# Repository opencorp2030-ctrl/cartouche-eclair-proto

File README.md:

# CARTOUCHE Drive

A small USB-C drive for an M.2 2230 NVMe SSD, built around the JMicron JMS583
bridge (USB 3.2 Gen 2, 10 Gb/s → PCIe Gen 3 ×2). It is the prototype drive for
[CARTOUCHE](https://cartouche.candygate.eu), a local AI that runs from a USB drive.

**Status:** schematic v0.1 (ERC 0). PCB v0.4 — 36 × 46 mm, 4 layers (In1 GND, In2 GND + 1.0 V island), 9 high-speed pairs as straight coupled pairs. Impedance from a 2D field solver (`tools/impedance.py`, JLC04161H-7628, with solder mask): USB 3.2 pairs 0.20/0.10 mm ≈ 86 Ω (target 90 Ω ±10 %), PCIe and REFCLK pairs 0.30/0.20 mm ≈ 89 Ω (target 85 Ω ±15 %), GND stitching. DRC: 0 unconnected, 0 schematic mismatch, 2 silkscreen warnings. Fabrication files in `hardware/fab/` (Gerbers zip, JLCPCB BOM and CPL). **Prototype, not verified:** JMS583 must be consigned (0 stock at JLCPCB), CPL rotations to check in the JLCPCB viewer, LED polarity assumed active-low.

## Blocks

| Block | Parts |
|---|---|
| USB-C (sink, 5 V) | Molex 105450-0101, CC pull-downs 5.1 kΩ, 100 nF on each SuperSpeed TX line |
| Bridge | JMS583 (QFN-64 8×8, 0.4 mm), 25 MHz crystal, REXT 12 kΩ 1 %, reset RC, SPI flash |
| Chip power | JMS583 internal regulators: 5 V → 1.0 V (buck, 4.7 µH) and 5 V → 3.3 V (LDO, chip only) |
| SSD power | TPS82130 3 A buck, 5 V → 3.3 V, 330 µF bulk |
| SSD | LOTES APCI0113 M.2 key M socket, 2 PCIe lanes, 220 nF on each PCIe TX line |

## Files

- `hardware/` — KiCad 9 project (`cartouche-drive.kicad_sch`), local libraries in `hardware/lib/`
- `hardware/cartouche-drive-schematic.pdf` — schematic export
- `tools/gen_schematic.py` — the connection list that generates the schematic
- `tools/build_pcb.py` — board, placement, planes and fan-out vias (KiCad Python)
- `tools/route_pcb.py` — net classes and Freerouting run

## References

- JMS583 datasheet PDS-17001 rev 1.0 (JMicron) — pin-out and required parts
- Part footprints: LCSC / EasyEDA libraries (LOTES C841669, Molex C134092, TPS82130 C473914)

## Sponsors

Thank you to the companies that support this open-source board:

- **[AISLER](https://aisler.net) is the PCB sponsor of this project** (boards, stencils and shipping, made in Europe). The AISLER logo is printed on the back of the board (placeholder on `B.Silkscreen`, `tools/aisler_logo.py`). Order your own with the button above.
- **[JMicron](https://www.jmicron.com)**, through its distributor **[BONMECK](https://www.bonmeck.com)**, provides free JMS583 bridge chip samples for the first prototypes.

Results of the prototypes, good or bad, will be published here.

## License

Open source. Hardware (`hardware/`, `docs/`): [CERN-OHL-S-2.0](LICENSE-HARDWARE). Tools (`tools/`): MIT.
See [LICENSE](LICENSE). Third-party libraries used in the KiCad project (KiCad standard libraries, LCSC/EasyEDA
footprints and 3D models) stay under their own licenses.

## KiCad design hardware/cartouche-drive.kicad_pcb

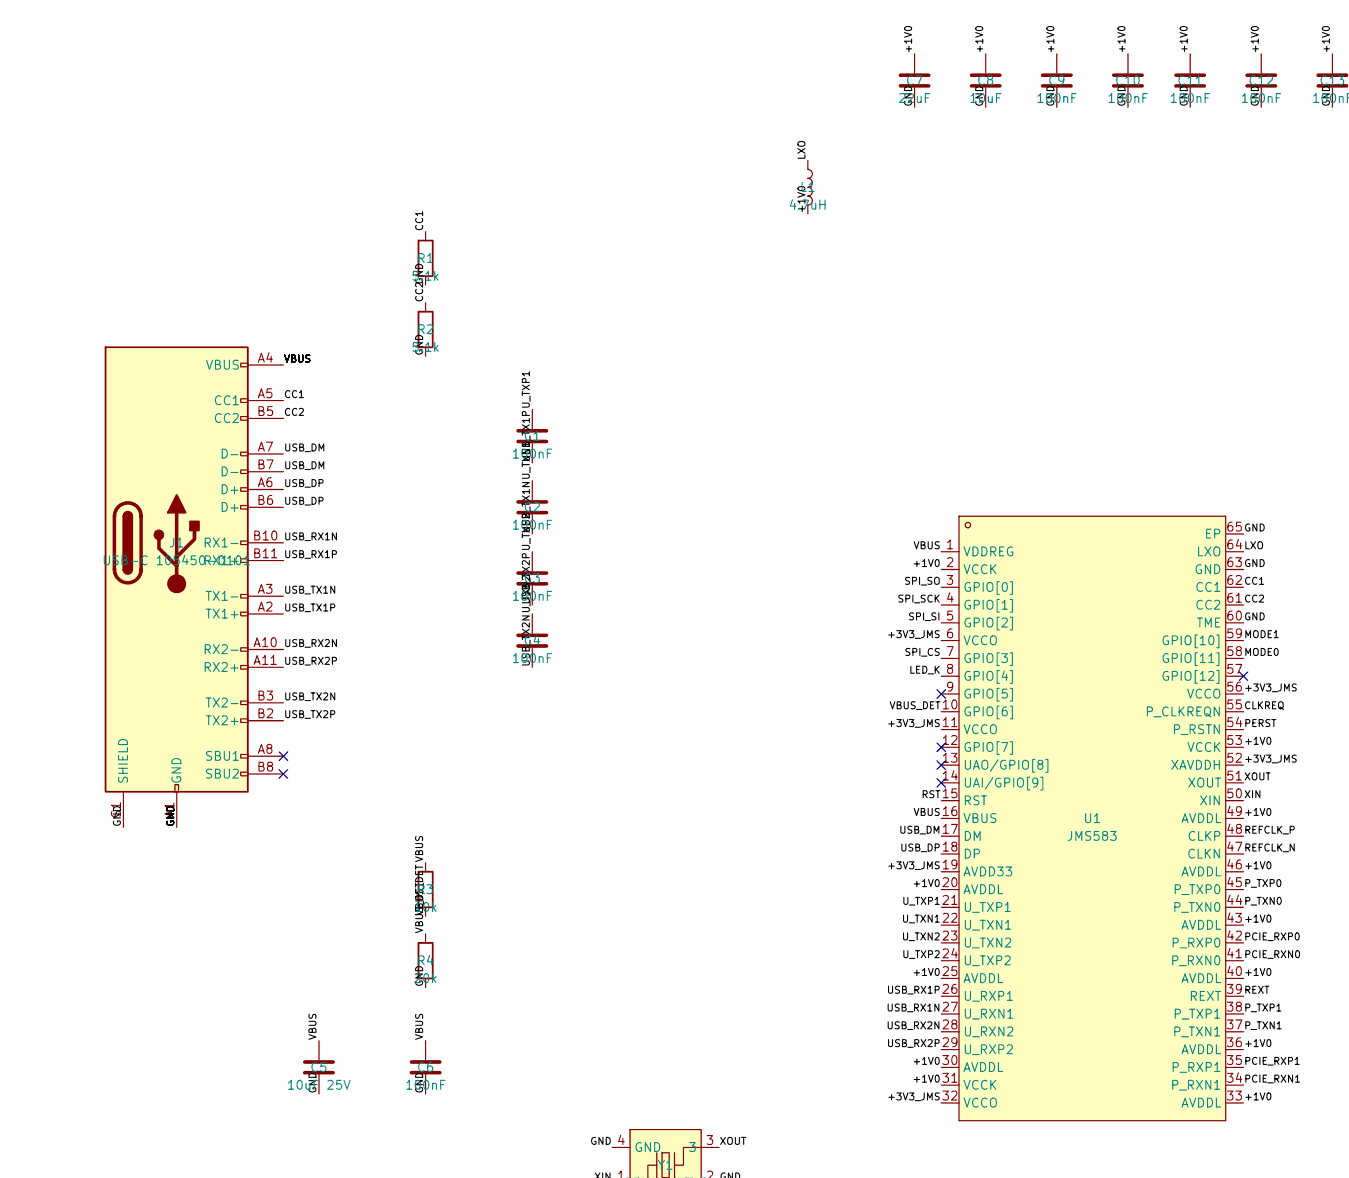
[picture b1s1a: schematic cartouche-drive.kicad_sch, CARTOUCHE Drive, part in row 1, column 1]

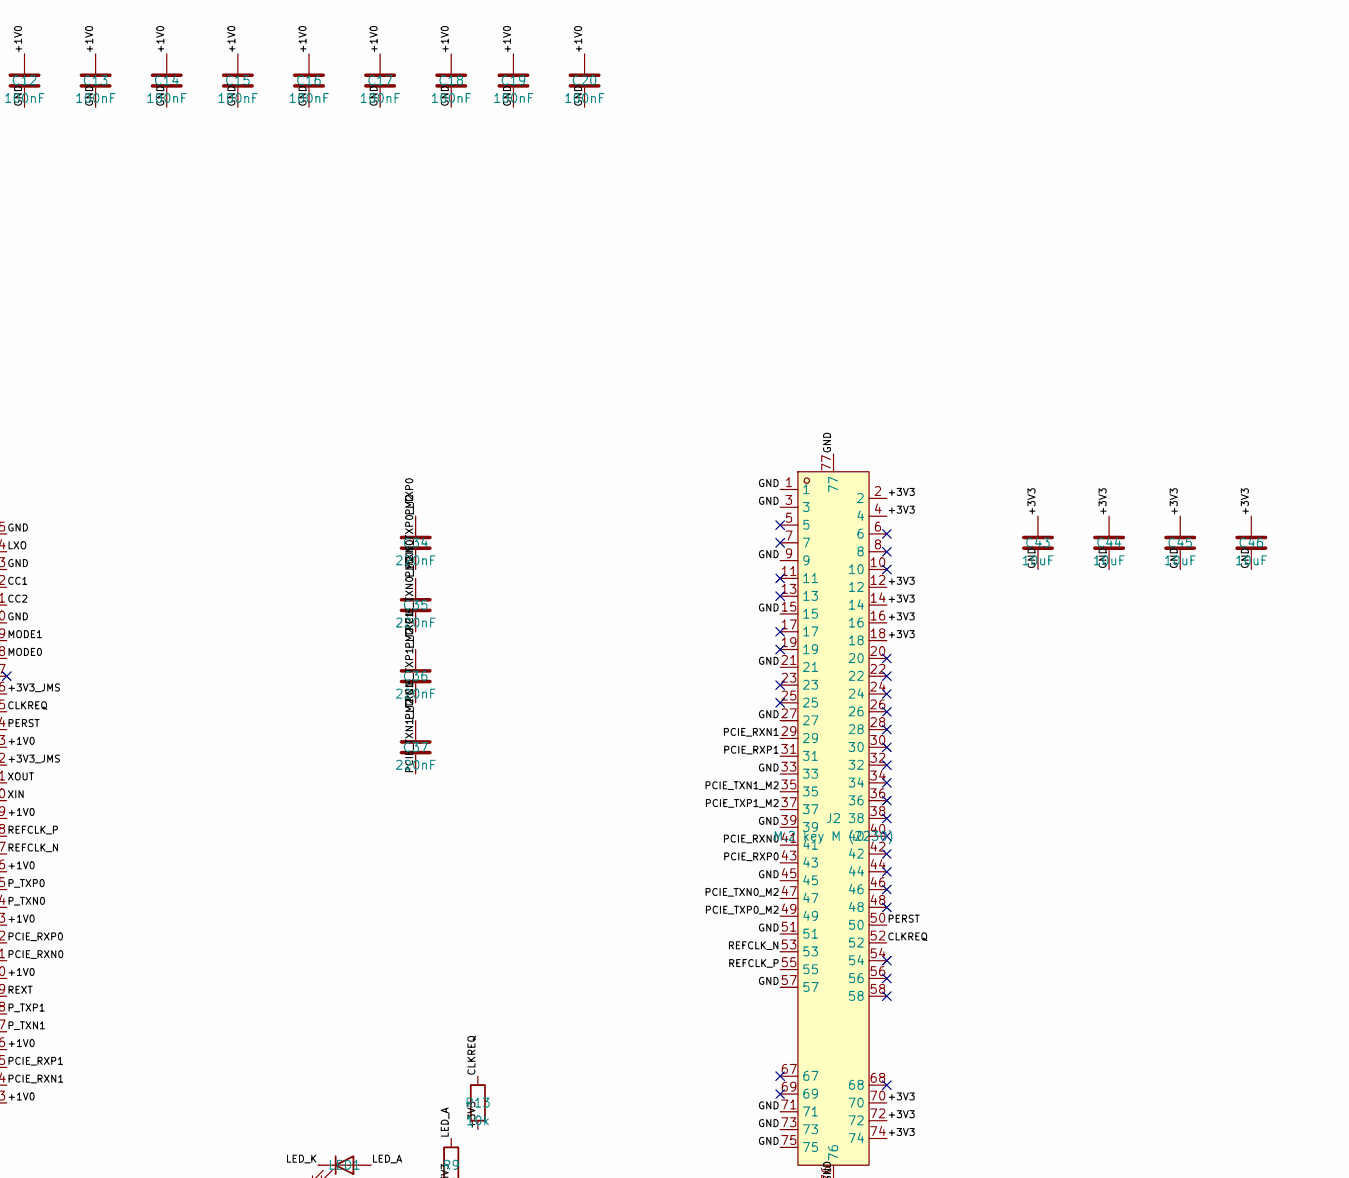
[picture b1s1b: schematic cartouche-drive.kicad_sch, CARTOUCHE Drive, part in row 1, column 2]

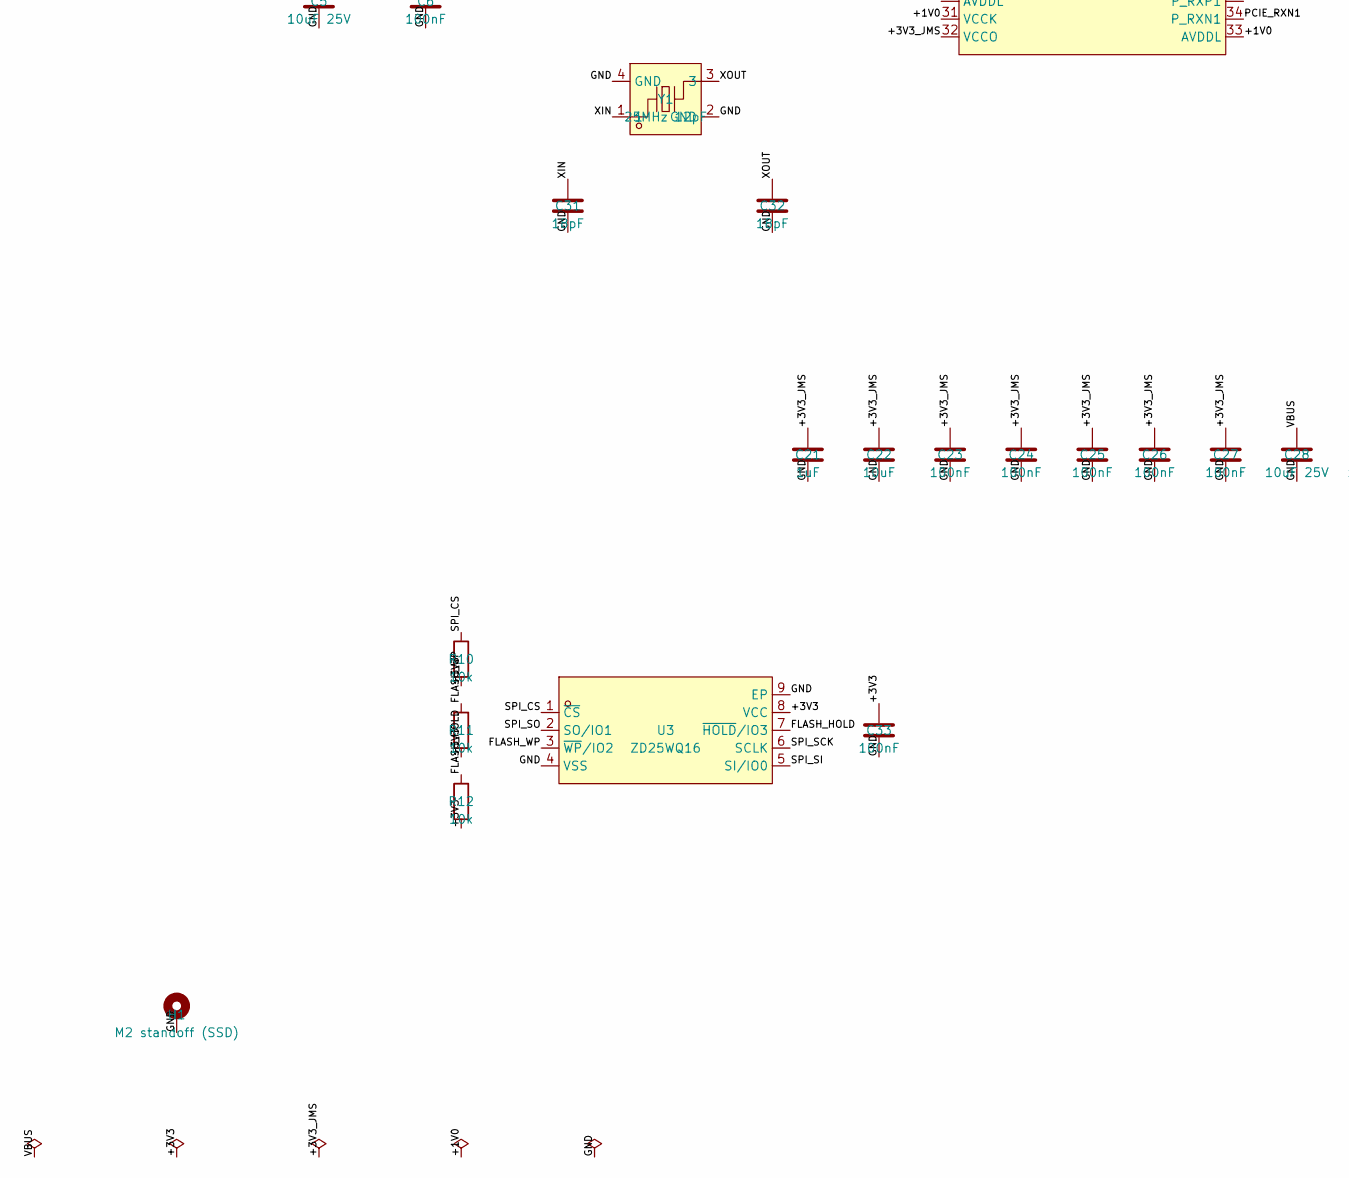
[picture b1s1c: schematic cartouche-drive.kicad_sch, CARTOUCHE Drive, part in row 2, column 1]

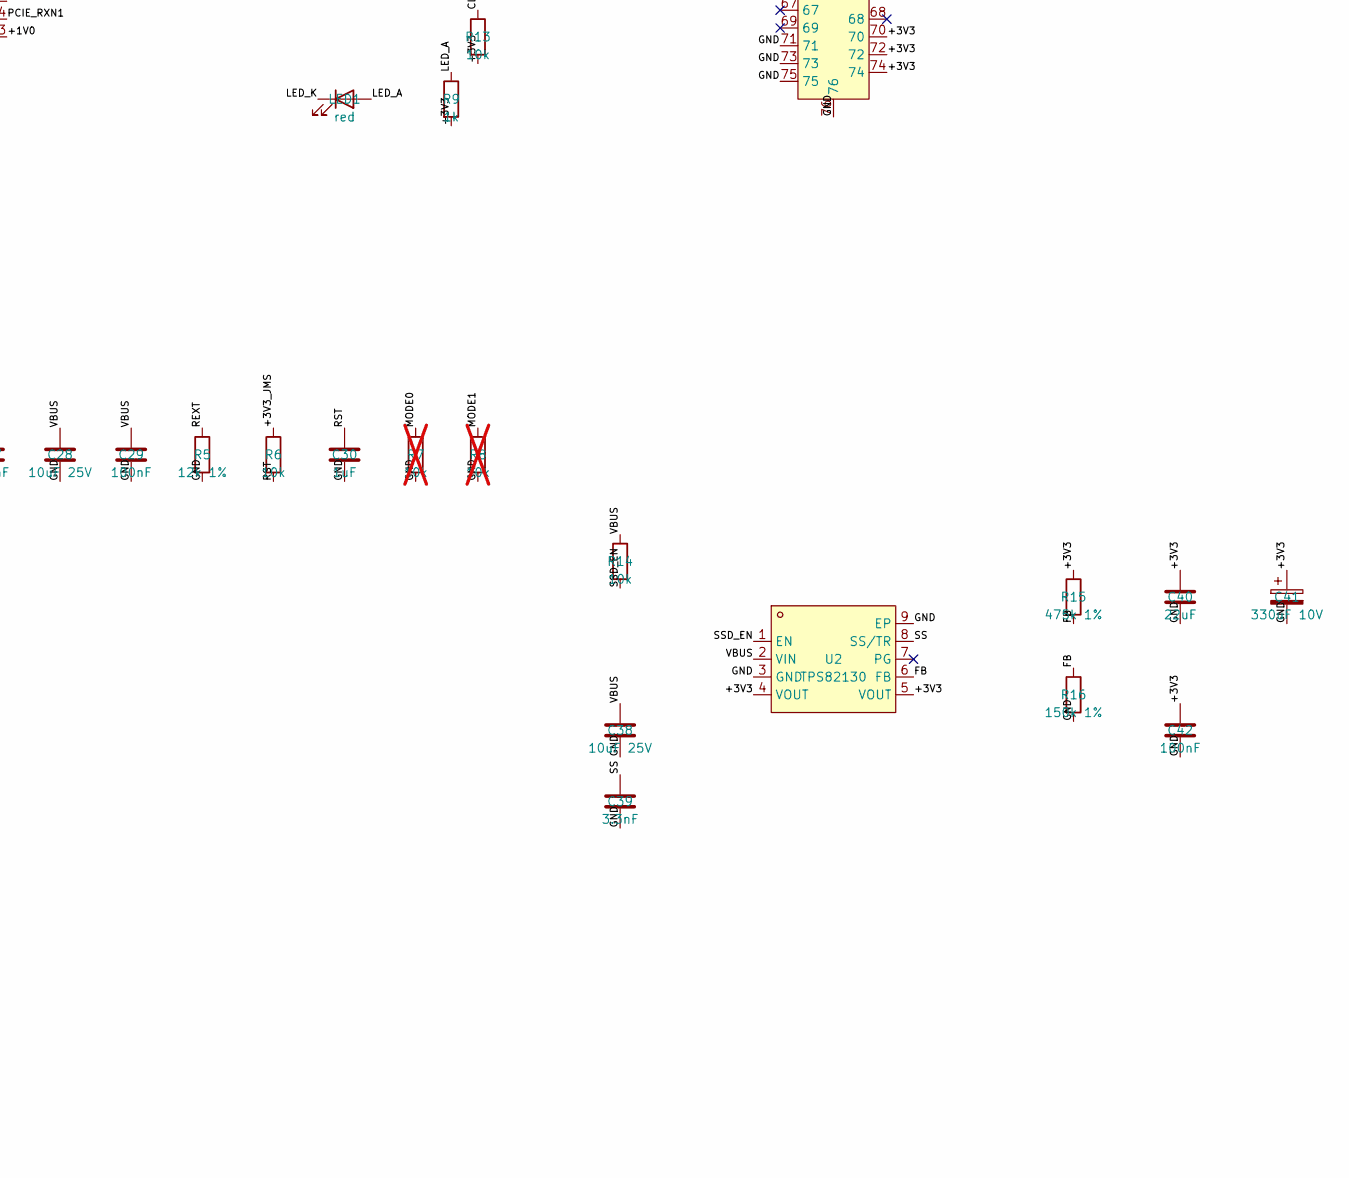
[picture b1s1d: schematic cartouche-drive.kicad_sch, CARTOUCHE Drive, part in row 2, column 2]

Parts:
C1, C2, C3, C4: 100nF; C_0201_0603Metric; LCSC C76934
C5, C28, C38: 10uF 25V; C_0805_2012Metric; LCSC C15850
C6, C9, C10, C11, C12, C13, C14, C15, C16, C17, C18, C19, C20, C23, C24, C25, C26, C27, C29, C33, C42: 100nF; C_0402_1005Metric; LCSC C1525
C7, C40: 22uF; C_0805_2012Metric; LCSC C45783
C8, C22, C43, C44, C45, C46: 10uF; C_0402_1005Metric; LCSC C15525
C21, C30: 1uF; C_0402_1005Metric; LCSC C52923
C31, C32: 18pF; C_0402_1005Metric; LCSC C1549
C34, C35, C36, C37: 220nF; C_0201_0603Metric; LCSC C76932
C39: 3.3nF; C_0402_1005Metric; LCSC C1536
C41: 330uF 10V; CP_EIA-7343-31_Kemet-D; LCSC C105408
H1: M2 standoff (SSD); MountingHole_2.2mm_M2_Pad_Via
J1: USB-C 105450-0101; USB_C_Receptacle_Molex_105450-0101; LCSC C134092
J2: M.2 key M (2230); CONN-SMD_APCI0113-P001A; LCSC C841669
L1: 4.7uH; L_1008_2520Metric; LCSC C383386
LED1: red; LED_0603_1608Metric; LCSC C2286
R1, R2: 5.1k; R_0402_1005Metric; LCSC C25905
R3, R6, R10, R11, R12, R13, R14: 10k; R_0402_1005Metric; LCSC C25744
R4: 20k; R_0402_1005Metric; LCSC C25765
R5: 12k 1%; R_0402_1005Metric; LCSC C25752
R7, R8: 10k; R_0402_1005Metric; LCSC C25744; not fitted
R9: 1k; R_0402_1005Metric; LCSC C11702
R15: 475k 1%; R_0402_1005Metric; LCSC C5713272
R16: 150k 1%; R_0402_1005Metric; LCSC C2909320
U1: JMS583; QFN-64_L8.0-W8.0-P0.40-TL-EP4.5; LCSC C9900110183
U2: TPS82130; USIP-8_L3.0-W2.8-P0.65-TL-EP; LCSC C473914
U3: ZD25WQ16; USON-8_L3.0-W2.0-P0.50-BL-EP; LCSC C7304007
Y1: 25MHz 12pF; CRYSTAL-SMD_4P-L1.6-W1.2-BL; LCSC C7301914

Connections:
/+1V0: C7.1, C8.1, C9.1, C10.1, C11.1, C12.1, C13.1, C14.1, C15.1, C16.1, C17.1, C18.1, C19.1, C20.1, L1.2, U1.2 (VCCK), U1.20 (AVDDL), U1.25 (AVDDL), U1.30 (AVDDL), U1.31 (VCCK), U1.33 (AVDDL), U1.36 (AVDDL), U1.40 (AVDDL), U1.43 (AVDDL), U1.46 (AVDDL), U1.49 (AVDDL), U1.53 (VCCK)
/+3V3: C33.1, C40.1, C41.1, C42.1, C43.1, C44.1, C45.1, C46.1, J2.2, J2.4, J2.12, J2.14, J2.16, J2.18, J2.70, J2.72, J2.74, R9.2, R10.2, R11.2, R12.2, R13.2, R15.1, U2.4 (VOUT), U2.5 (VOUT), U3.8 (VCC)
/+3V3_JMS: C21.1, C22.1, C23.1, C24.1, C25.1, C26.1, C27.1, R6.1, U1.6 (VCCO), U1.11 (VCCO), U1.19 (AVDD33), U1.32 (VCCO), U1.52 (XAVDDH), U1.56 (VCCO)
/CC1: J1.A5 (CC1), R1.1, U1.62 (CC1)
/CC2: J1.B5 (CC2), R2.1, U1.61 (CC2)
/CLKREQ: J2.52, R13.1, U1.55 (P_CLKREQN)
/FB: R15.2, R16.1, U2.6 (FB)
/FLASH_HOLD: R12.1, U3.7 (~HOLD/IO3)
/FLASH_WP: R11.1, U3.3 (~WP/IO2)
/GND: C5.2, C6.2, C7.2, C8.2, C9.2, C10.2, C11.2, C12.2, C13.2, C14.2, C15.2, C16.2, C17.2, C18.2, C19.2, C20.2, C21.2, C22.2, C23.2, C24.2, C25.2, C26.2, C27.2, C28.2, C29.2, C30.2, C31.2, C32.2, C33.2, C38.2, C39.2, C40.2, C41.2, C42.2, C43.2, C44.2, C45.2, C46.2, H1.1, J1.A1 (GND), J1.A12 (GND), J1.B1 (GND), J1.B12 (GND), J1.S1 (SHIELD), J2.1, J2.3, J2.9, J2.15, J2.21, J2.27, J2.33, J2.39, J2.45, J2.51, J2.57, J2.71, J2.73, J2.75, J2.76, J2.77, R1.2, R2.2, R4.2, R5.2, R7.2, R8.2, R16.2, U1.60 (TME), U1.63 (GND), U1.65 (EP), U2.3 (GND), U2.9 (EP), U3.4 (VSS), U3.9 (EP), Y1.2 (GND), Y1.4 (GND)
/LED_A: LED1.2 (A), R9.1
/LED_K: LED1.1 (K), U1.8 (GPIO[4])
/LXO: L1.1, U1.64 (LXO)
/MODE0: R7.1, U1.58 (GPIO[11])
/MODE1: R8.1, U1.59 (GPIO[10])
/PCIE_RXN0: J2.41, U1.41 (P_RXN0)
/PCIE_RXN1: J2.29, U1.34 (P_RXN1)
/PCIE_RXP0: J2.43, U1.42 (P_RXP0)
/PCIE_RXP1: J2.31, U1.35 (P_RXP1)
/PCIE_TXN0_M2: C35.2, J2.47
/PCIE_TXN1_M2: C37.2, J2.35
/PCIE_TXP0_M2: C34.2, J2.49
/PCIE_TXP1_M2: C36.2, J2.37
/PERST: J2.50, U1.54 (P_RSTN)
/P_TXN0: C35.1, U1.44 (P_TXN0)
/P_TXN1: C37.1, U1.37 (P_TXN1)
/P_TXP0: C34.1, U1.45 (P_TXP0)
/P_TXP1: C36.1, U1.38 (P_TXP1)
/REFCLK_N: J2.53, U1.47 (CLKN)
/REFCLK_P: J2.55, U1.48 (CLKP)
/REXT: R5.1, U1.39 (REXT)
/RST: C30.1, R6.2, U1.15 (RST)
/SPI_CS: R10.1, U1.7 (GPIO[3]), U3.1 (~CS)
/SPI_SCK: U1.4 (GPIO[1]), U3.6 (SCLK)
/SPI_SI: U1.5 (GPIO[2]), U3.5 (SI/IO0)
/SPI_SO: U1.3 (GPIO[0]), U3.2 (SO/IO1)
/SS: C39.1, U2.8 (SS/TR)
/SSD_EN: R14.2, U2.1 (EN)
/USB_DM: J1.A7 (D-), J1.B7 (D-), U1.17 (DM)
/USB_DP: J1.A6 (D+), J1.B6 (D+), U1.18 (DP)
/USB_RX1N: J1.B10 (RX1-), U1.27 (U_RXN1)
/USB_RX1P: J1.B11 (RX1+), U1.26 (U_RXP1)
/USB_RX2N: J1.A10 (RX2-), U1.28 (U_RXN2)
/USB_RX2P: J1.A11 (RX2+), U1.29 (U_RXP2)
/USB_TX1N: C2.2, J1.A3 (TX1-)
/USB_TX1P: C1.2, J1.A2 (TX1+)
/USB_TX2N: C4.2, J1.B3 (TX2-)
/USB_TX2P: C3.2, J1.B2 (TX2+)
/U_TXN1: C2.1, U1.22 (U_TXN1)
/U_TXN2: C4.1, U1.23 (U_TXN2)
/U_TXP1: C1.1, U1.21 (U_TXP1)
/U_TXP2: C3.1, U1.24 (U_TXP2)
/VBUS: C5.1, C6.1, C28.1, C29.1, C38.1, J1.A4 (VBUS), J1.A9 (VBUS), J1.B4 (VBUS), J1.B9 (VBUS), R3.1, R14.1, U1.1 (VDDREG), U1.16 (VBUS), U2.2 (VIN)
/VBUS_DET: R3.2, R4.1, U1.10 (GPIO[6])
/XIN: C31.1, U1.50 (XIN), Y1.1
/XOUT: C32.1, U1.51 (XOUT), Y1.3

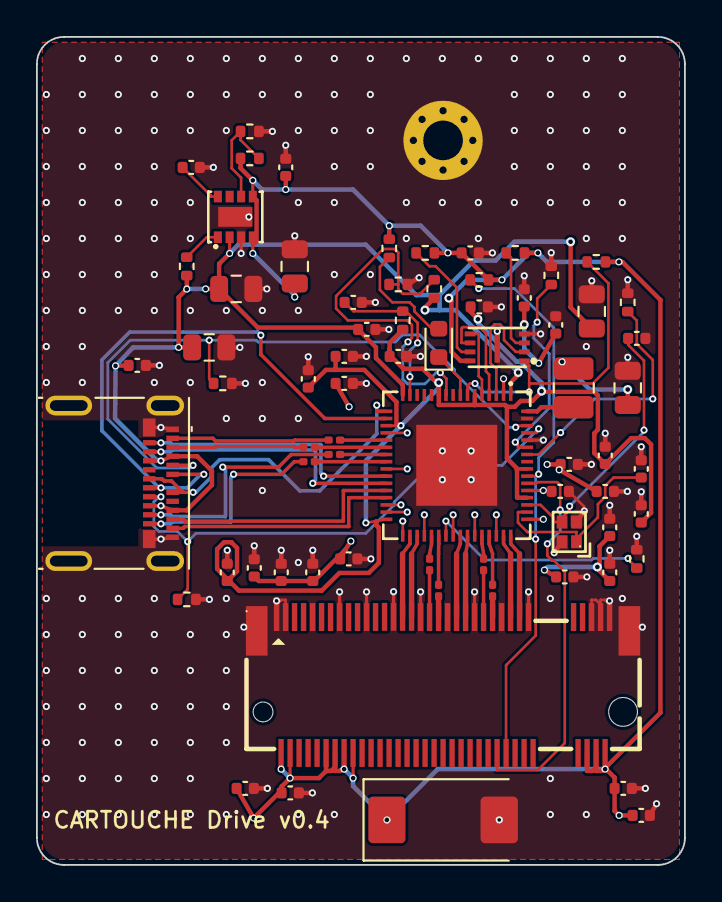
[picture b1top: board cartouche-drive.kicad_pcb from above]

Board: 4 copper layers, 36.0 x 46.0 mm, 71 parts (0 on the bottom side), 56 nets.

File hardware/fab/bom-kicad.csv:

"Reference","Value","Footprint","LCSC","QUANTITY","DNP"
"C1-C4","100nF","Capacitor_SMD:C_0201_0603Metric","C76934","4",""
"C5,C28,C38","10uF 25V","Capacitor_SMD:C_0805_2012Metric","C15850","3",""
"C6,C9-C20,C23-C27,C29,C33,C42","100nF","Capacitor_SMD:C_0402_1005Metric","C1525","21",""
"C7,C40","22uF","Capacitor_SMD:C_0805_2012Metric","C45783","2",""
"C8,C22,C43-C46","10uF","Capacitor_SMD:C_0402_1005Metric","C15525","6",""
"C21,C30","1uF","Capacitor_SMD:C_0402_1005Metric","C52923","2",""
"C31,C32","18pF","Capacitor_SMD:C_0402_1005Metric","C1549","2",""
"C34-C37","220nF","Capacitor_SMD:C_0201_0603Metric","C76932","4",""
"C39","3.3nF","Capacitor_SMD:C_0402_1005Metric","C1536","1",""
"C41","330uF 10V","Capacitor_Tantalum_SMD:CP_EIA-7343-31_Kemet-D","C105408","1",""
"J1","USB-C 105450-0101","Connector_USB:USB_C_Receptacle_Molex_105450-0101","C134092","1",""
"J2","M.2 key M (2230)","cartouche:CONN-SMD_APCI0113-P001A","C841669","1",""
"L1","4.7uH","Inductor_SMD:L_1008_2520Metric","C383386","1",""
"LED1","red","LED_SMD:LED_0603_1608Metric","C2286","1",""
"R1,R2","5.1k","Resistor_SMD:R_0402_1005Metric","C25905","2",""
"R3,R6,R10-R14","10k","Resistor_SMD:R_0402_1005Metric","C25744","7",""
"R4","20k","Resistor_SMD:R_0402_1005Metric","C25765","1",""
"R5","12k 1%","Resistor_SMD:R_0402_1005Metric","C25752","1",""
"R9","1k","Resistor_SMD:R_0402_1005Metric","C11702","1",""
"R15","475k 1%","Resistor_SMD:R_0402_1005Metric","C5713272","1",""
"R16","150k 1%","Resistor_SMD:R_0402_1005Metric","C2909320","1",""
"U1","JMS583","cartouche:QFN-64_L8.0-W8.0-P0.40-TL-EP4.5","C9900110183","1",""
"U2","TPS82130","cartouche:USIP-8_L3.0-W2.8-P0.65-TL-EP","C473914","1",""
"U3","ZD25WQ16","cartouche:USON-8_L3.0-W2.0-P0.50-BL-EP","C7304007","1",""
"Y1","25MHz 12pF","cartouche:CRYSTAL-SMD_4P-L1.6-W1.2-BL","C7301914","1",""
